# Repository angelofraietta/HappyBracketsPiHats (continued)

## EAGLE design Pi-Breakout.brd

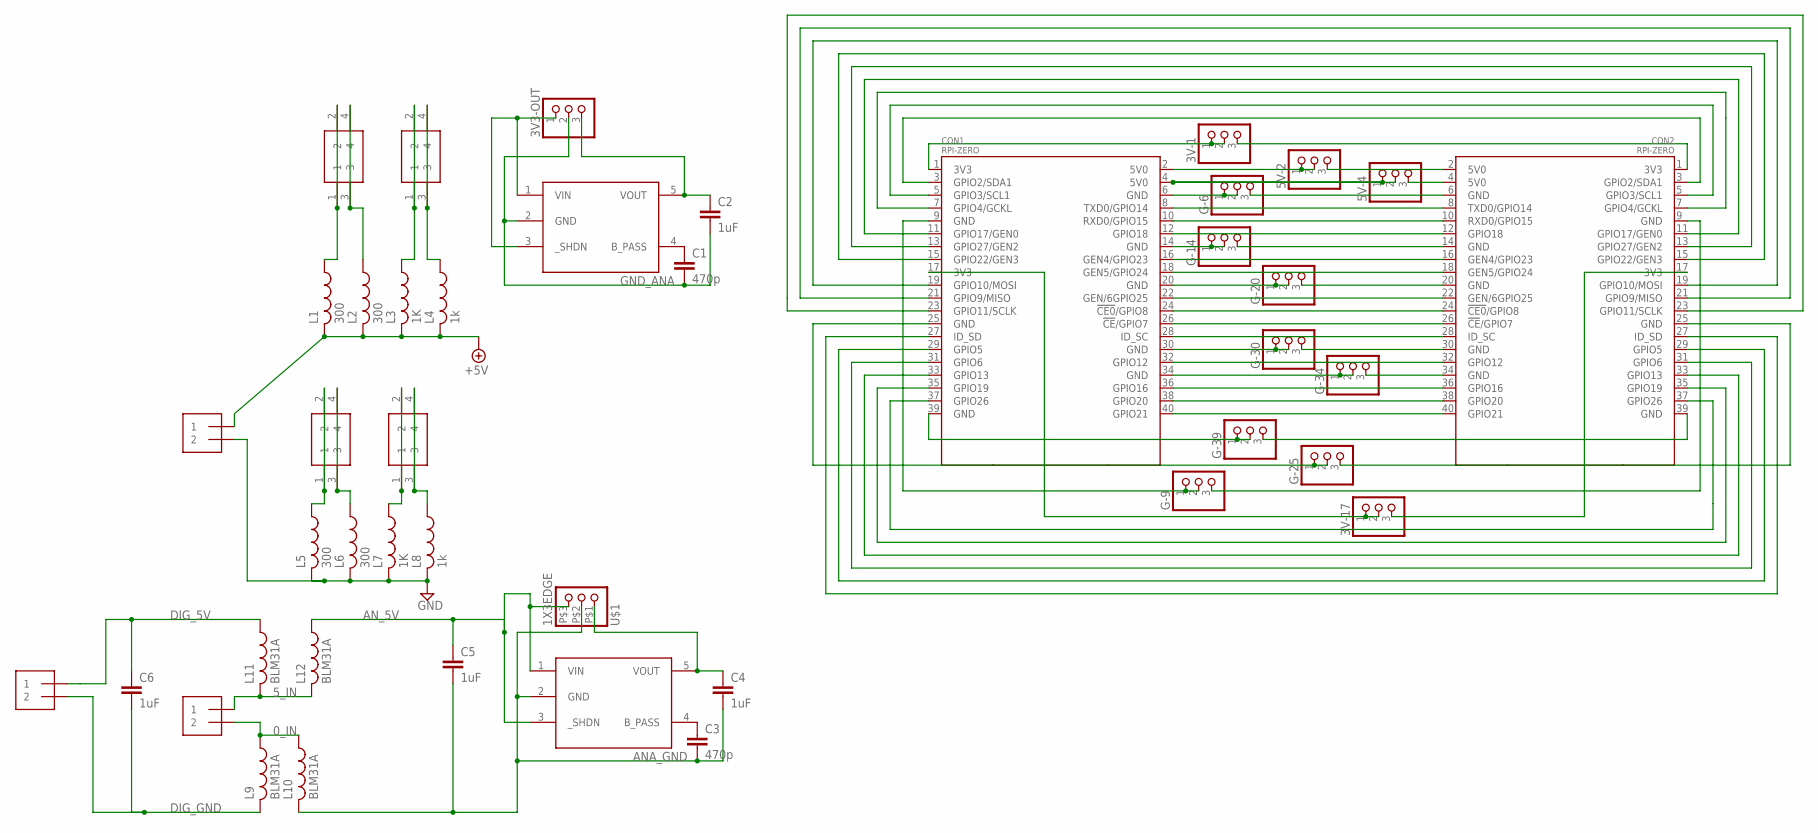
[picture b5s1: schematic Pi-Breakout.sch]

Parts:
3V3-OUT, 3V-1, 3V-17, 5V-2, 5V-4: PINHD-1X3; 1X03
5V1, 5V2: 2X2HEADER; 2X2
C1, C3: 470p; C0603
C2, C4, C5, C6: 1uF; C0603
CON1, CON2: RPI-ZERO; RASPBERRYPI_BASTELSTUBE_V13_RASPI_BOARD_B+_FULL
G-6, G-9, G-14, G-20, G-25, G-30, G-34, G-39: PINHD-1X3; 1X03
GND1, GND2: 2X2HEADER; 2X2
J1: 2X1-LOCKING; 22-23-2021
J2, J3: 1X2EDGE; 1X2_EDGE
L1, L2, L5, L6: 300; SML1206
L3, L7: 1K; SML1206
L4, L8: 1k; SML1206
L9, L10, L11, L12: BLM31A; SML1206
U1, U2: TC1014-3.3V; GHI-IC_SOT23-5(MICROCHIP)
U$1: 1X3EDGE; 1X3_EDGE

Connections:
0_IN: J2.P$2 (2), L9.A (1), L10.A (1)
3V3_1_B: 3V-1.1, 3V-1.2, CON1.1 (3V3)
3V3_1_PI: 3V-1.3, CON2.1 (3V3)
3V3_17_B: 3V-17.1, 3V-17.2, CON1.17 (3V3)
3V3_17_PI: 3V-17.3, CON2.17 (3V3)
5V0_B: 5V-2.1, 5V-2.2, CON1.2 (5V0)
5V0_PI: 5V-2.3, CON2.2 (5V0)
5V1_B: 5V-4.1, 5V-4.2, CON1.4 (5V0)
5V1_PI: 5V-4.3, CON2.4 (5V0)
5_IN: J2.P$1 (1), L11.C (2), L12.C (2)
+5V: J1.1, L1.C (2), L2.C (2), L3.C (2), L4.C (2)
ANA_GND: C3.2, C4.2, C5.2, L10.C (2), U2.2 (GND), U$1.P$2 (2)
AN_5V: C5.1, L12.A (1), U2.1 (VIN), U2.3 (_SHDN), U$1.P$3 (3)
DIG_5V: C6.1, J3.P$1 (1), L11.A (1)
DIG_GND: C6.2, J3.P$2 (2), L9.C (2)
GND: J1.2, L5.C (2), L6.C (2), L7.C (2), L8.C (2)
GND1: GND1.1, GND1.2, L5.A (1)
GND@7: CON1.34 (GND), G-34.1, G-34.2
GND_6_B: CON1.6 (GND), G-6.1, G-6.2
GND_6_PI: CON2.6 (GND), G-6.3
GND_9_B: CON1.9 (GND), G-9.1, G-9.2
GND_9_PI: CON2.9 (GND), G-9.3
GND_14_B: CON1.14 (GND), G-14.1, G-14.2
GND_14_PI: CON2.14 (GND), G-14.3
GND_20_B: CON1.20 (GND), G-20.1, G-20.2
GND_20_PI: CON2.20 (GND), G-20.3
GND_25_B: CON1.25 (GND), G-25.1, G-25.2
GND_25_PI: CON2.25 (GND), G-25.3
GND_30_B: CON1.30 (GND), G-30.1, G-30.2
GND_30_PI: CON2.30 (GND), G-30.3
GND_34_PI: CON2.34 (GND), G-34.3
GND_39_B: CON1.39 (GND), G-39.1, G-39.2
GND_39_PI: CON2.39 (GND), G-39.3
GND_ANA: 3V3-OUT.2, C1.2, C2.2, U1.2 (GND)
unnamed: CON1.8 (TXD0/GPIO14), CON2.8 (TXD0/GPIO14)
unnamed: CON1.10 (RXD0/GPIO15), CON2.10 (RXD0/GPIO15)
unnamed: CON1.12 (GPIO18), CON2.12 (GPIO18)
unnamed: CON1.16 (GEN4/GPIO23), CON2.16 (GEN4/GPIO23)
unnamed: CON1.18 (GEN5/GPIO24), CON2.18 (GEN5/GPIO24)
unnamed: CON1.22 (GEN/6GPIO25), CON2.22 (GEN/6GPIO25)
unnamed: CON1.24 (!CE0!/GPIO8), CON2.24 (!CE0!/GPIO8)
unnamed: CON1.26 (!CE!/GPIO7), CON2.26 (!CE!/GPIO7)
unnamed: CON1.28 (ID_SC), CON2.28 (ID_SC)
unnamed: CON1.32 (GPIO12), CON2.32 (GPIO12)
unnamed: CON1.36 (GPIO16), CON2.36 (GPIO16)
unnamed: CON1.38 (GPIO20), CON2.38 (GPIO20)
unnamed: CON1.40 (GPIO21), CON2.40 (GPIO21)
unnamed: CON1.3 (GPIO2/SDA1), CON2.3 (GPIO2/SDA1)
unnamed: CON1.5 (GPIO3/SCL1), CON2.5 (GPIO3/SCL1)
unnamed: CON1.7 (GPIO4/GCKL), CON2.7 (GPIO4/GCKL)
unnamed: CON1.11 (GPIO17/GEN0), CON2.11 (GPIO17/GEN0)
unnamed: CON1.13 (GPIO27/GEN2), CON2.13 (GPIO27/GEN2)
unnamed: CON1.15 (GPIO22/GEN3), CON2.15 (GPIO22/GEN3)
unnamed: CON1.19 (GPIO10/MOSI), CON2.19 (GPIO10/MOSI)
unnamed: CON1.21 (GPIO9/MISO), CON2.21 (GPIO9/MISO)
unnamed: CON1.23 (GPIO11/SCLK), CON2.23 (GPIO11/SCLK)
unnamed: CON1.37 (GPIO26), CON2.37 (GPIO26)
unnamed: CON1.35 (GPIO19), CON2.35 (GPIO19)
unnamed: CON1.31 (GPIO6), CON2.31 (GPIO6)
unnamed: CON1.33 (GPIO13), CON2.33 (GPIO13)
unnamed: CON1.29 (GPIO5), CON2.29 (GPIO5)
unnamed: CON1.27 (ID_SD), CON2.27 (ID_SD)
unnamed: GND1.3, GND1.4, L6.A (1)
unnamed: GND2.1, GND2.2, L7.A (1)
unnamed: GND2.3, GND2.4, L8.A (1)
unnamed: 5V1.1, 5V1.2, L1.A (1)
unnamed: 5V1.3, 5V1.4, L2.A (1)
unnamed: 5V2.1, 5V2.2, L3.A (1)
unnamed: 5V2.3, 5V2.4, L4.A (1)
unnamed: 3V3-OUT.1, U1.1 (VIN), U1.3 (_SHDN)
unnamed: C1.1, U1.4 (B_PASS)
unnamed: 3V3-OUT.3, C2.1, U1.5 (VOUT)
unnamed: C4.1, U2.5 (VOUT), U$1.P$1 (1)
unnamed: C3.1, U2.4 (B_PASS)

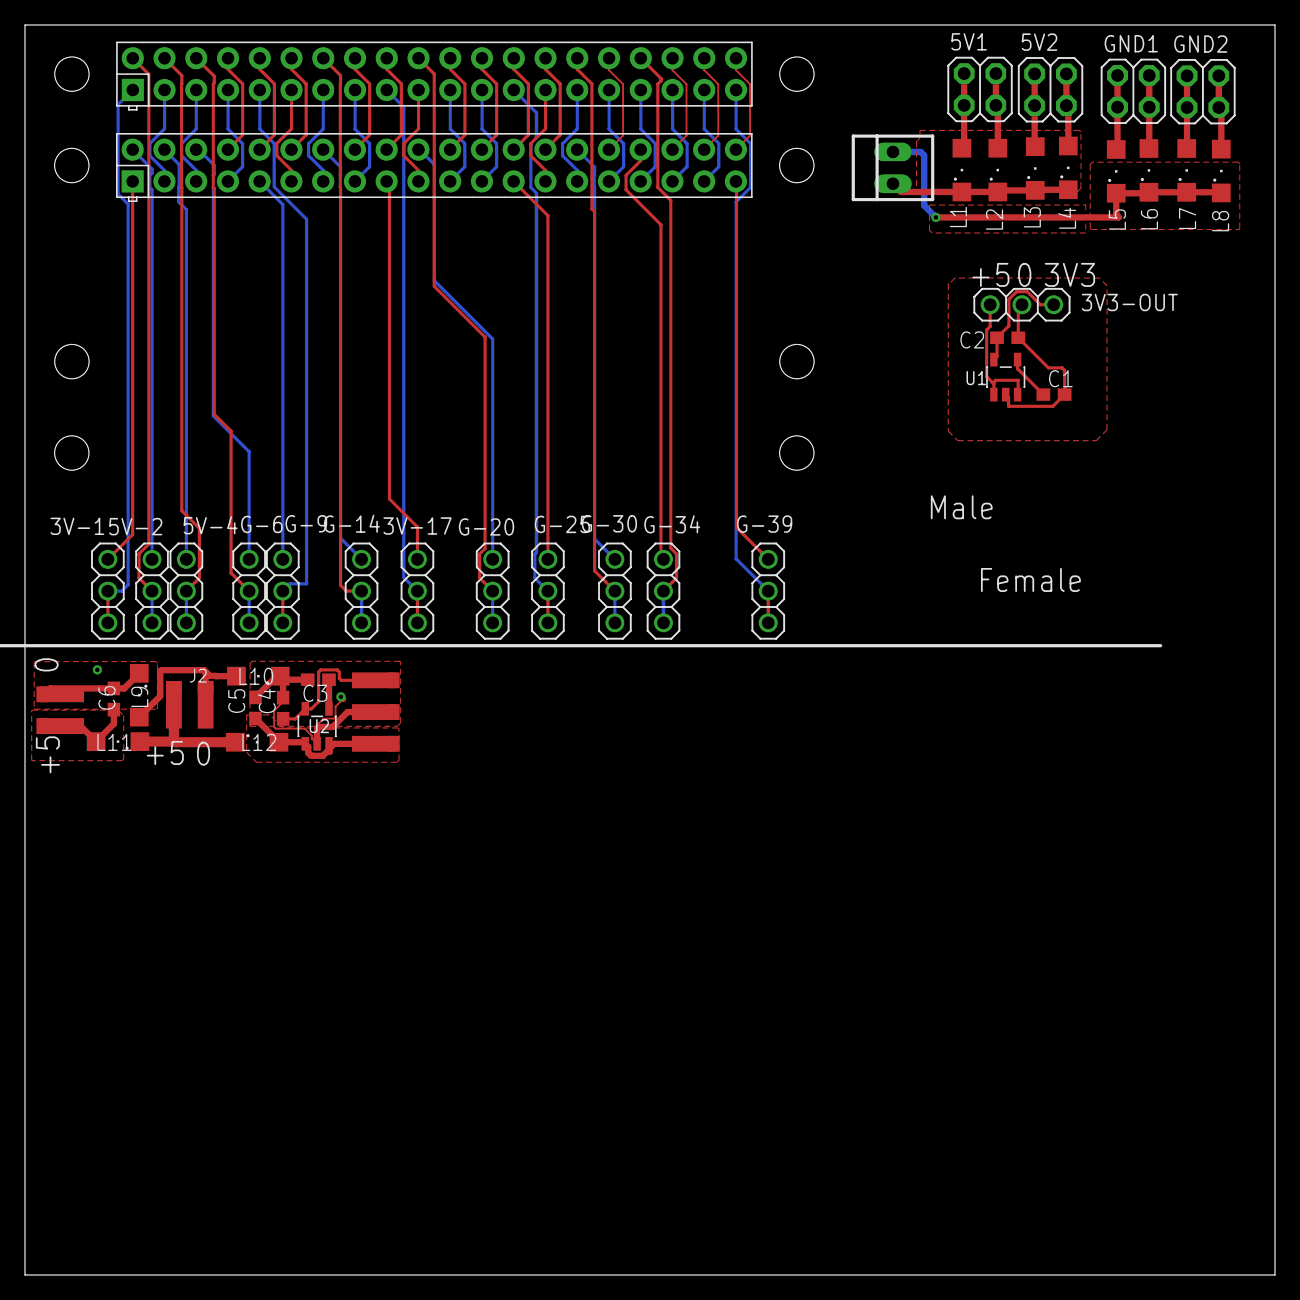
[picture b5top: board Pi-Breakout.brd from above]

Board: 2 copper layers, 100.0 x 100.0 mm, 43 parts (0 on the bottom side), 74 nets.

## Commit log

2018-09-11 Added Project Base
2018-09-11 add description
2018-09-11 added compondents
2018-09-12 Added Board
2018-09-21 Added I2C and Amplifier
2018-09-24 Renumbered Pins Placed components for first board
2018-09-24 Pre-resync board and schematic There is board inconsitency
2018-09-24 Consistency put back Removed GND pour from top
2018-09-25 Applied star Power
2018-09-26 Changed Ferrite Beads
2018-09-26 Routed all but power
2018-09-26 Added LED
2018-09-27 Pre- grove connector
2018-09-27 PostGrove
2018-09-27 Romoved Script
2018-09-27 Rout complete and rats nest. Need to complete pour
2018-09-27 Completed Ratsnets
2018-09-27 Changed Polygons so we had maximum pour
2018-09-27 Added GPIO Text
2018-09-27 Renumbered parts and aligned text
2018-09-27 Added Title Block
2018-09-28 Added I2Sboard
2018-09-28 Performed layout
2018-10-01 added i2C
2018-10-01 added LED pin displays
2018-10-02 Changed capacitor footprints
2018-10-02 Completed route
2018-10-02 added AGND polygon
2018-10-02 added additional polygon
2018-10-02 Added Titleblock
2018-10-02 changed component values so they are consistent
2018-10-02 Added Bill of Materials
2018-10-03 Added GerberFiles
2018-10-03 BOM as Text
2018-10-03 Added BOM
2018-10-06 Changed Capacitor sizes for tant caps
2018-10-06 Updated BOM
2018-10-07 Added gnd to SCK pin
2018-10-07 Corrected Speaker pin text
2018-10-07 Added Pam 8403
2018-10-07 Fit Charger Parts
2018-10-08 Routed to Audio
2018-10-08 Routed with ratsnest
2018-10-08 Changed Footprints for consistency
2018-10-08 Updated Capacitor footprint
2018-10-08 Changed Current Resistor to 100K
2018-10-08 Made Values consistent with Upper case K
2018-10-09 Updated Component value
2018-10-09 Changed the name of RPI Header
2018-10-09 Removed csv
2018-10-09 Added Slikscreen
2018-10-09 Added I2C to silkscreen
2018-10-09 updated fomts
2018-10-30 Swapped position of Mosfet Capacitively coupled Audio Set OE of I2C translator to GND Set Mute so it floats to +5
2018-10-30 Adjusted Layout
2018-10-31 Build Revision 1
2018-10-31 Added R14 10K resistance to translator
2018-11-01 Updated BOM and zip
2018-11-01 Added Image1.jpg
2018-12-28 Added Breakout
2018-12-29 Added Second CIRCUIT
2020-03-31 Update for Move account
2020-05-15 Added PiZeroHifi
2020-05-15 CHanged to Use Angelo version of HappyBrackets library
2020-07-31 Added Hifi Board
2020-08-05 Route HifiBoard
2020-08-05 Change position of GPIO
2020-08-05 Revert "Added Hifi Board"
    This reverts commit 465897fff771744b6bd4fb0467af0f24cf217bbb.
